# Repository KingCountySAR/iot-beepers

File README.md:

# SAR Beepers

A dedicated, loud pager for SAR callouts. It's a cheap ESP32 box on the member's home Wi-Fi with a buzzer alarm, status and alert LEDs, a button and an arm/quiet switch. The central server forwards pages to it, tracks who received and acknowledged them, monitors device health, and pushes firmware updates.

```
 callout source ──POST /api/ingest/page──┐
 web UI "Send page" ─────────────────────┤
                                         ▼
                ┌───────────────────────────────────────┐
                │ server (Node, Hono)                   │
                │  • REST API + React web UI            │      wss://host/mqtt
                │  • embedded MQTT broker (aedes) ──────┼──────────────────────► pagers
                │  • Postgres (Drizzle)                 │◄── status/ack/events ──
                │  • firmware store + OTA rollout       │
                └───────────────────────────────────────┘
```

| Dir | What |
|---|---|
| `server/` | Hono API, embedded MQTT broker, Drizzle/Postgres. Tests in `server/test` |
| `web/` | Vite + React admin and member UI |
| `firmware/` | ESP-IDF app ([firmware/README.md](firmware/README.md)) |
| `deploy/` | Its app on the KCSARA VM (the [vm](../vm) repo) |
| `hardware/` | Carrier board for the XIAO ESP32C3 ([rev1](hardware/rev1/README.md)) |
| `docs/` | [protocol](docs/protocol.md), [hardware behaviour](docs/hardware.md), [metrics](docs/metrics.md) |

## How a member sets up a pager
1. Plug it in. The green LED is mostly on: it's in setup mode.
2. On a phone, join the `SAR-Pager-xxxx` Wi-Fi. The setup page opens; if it doesn't, browse to `http://192.168.4.1`.
3. Choose the home Wi-Fi, enter its password, and confirm the server URL. The pager joins the network, registers with the server, and shows a **pairing code** and link.
4. Rejoin home Wi-Fi, open the link, sign in, and pick which channels the pager should alarm for.
5. The green LED settles to a short blip every 5 s. Press the button: one chirp means all good.

Pairing happens on the server, never on the device. The pager only holds a random secret, so no member passwords live on it. Channel choices are made from any browser, and a replacement pager is just a re-pair.

## Design notes
- **Embedded broker.** For 20–100 devices, an in-process MQTT broker means one container and no broker credentials to keep in sync. Device auth checks the DB directly. Each device can only use its own `dev/<id>/…` topics.
- **MQTT over WebSocket on 443.** One port and one TLS certificate (the VM's Caddy and Let's Encrypt), and it gets through hotel/guest networks.
- **Delivery tracking.** Every page has per-device *sent / received / acknowledged* timestamps. Devices that were offline get unexpired pages replayed when they reconnect. Pages older than 10 min arrive silently (LED only), so nobody gets a 3 am alarm for yesterday's mission.
- **Silent failure is the enemy.** The dashboard lists paired pagers that are offline, and the pager itself chirps if it can't reach the server for 30 min.
- **OTA with rollback.** Uploaded images are validated (project name and version are read from the image). You can pin one device to a version to canary it, then make it the default. A bad image rolls itself back.
- **Postgres in production, PGlite in dev/tests.** With no `DATABASE_URL`, the server runs Postgres-in-WASM in-process, so there's nothing to install locally. It runs the same SQL and migrations.

## Development
Requires Node 22+.

```sh
npm install
cp server/.env.example server/.env.local   # then put your email in SITE_ADMINS
npm run dev                          # UI :4100 (Vite, proxies /api and /mqtt to the server on :4102), metrics :4101
npm test                             # server integration tests (PGlite)
TEST_DATABASE_URL=postgres://postgres:pw@localhost:5432/postgres npm test   # same, against real Postgres
```

Open http://localhost:4100 and sign in with your `SITE_ADMINS` email. In dev, `DEV_LOGIN=true` lets you type an email instead of going through Google (treated as managed by its address's domain, which must be one of `ALLOWED_DOMAINS`). Create a channel, then pair a device.

The UI is on :4100 and metrics on :4101 in production too. Dev ports and URLs come from `server/dev.env`; `server/.env` overrides them, and `server/.env.local` (gitignored, for your own settings) overrides both.

**Without hardware**, simulate a device with the helpers in `server/test/harness.ts`. They do the same register → MQTT → hello flow as the firmware.

**Schema changes:** edit `server/src/db/schema.ts`. Until the first release we don't keep migrations: delete `server/drizzle/`, run `npm run db:generate -w server` to regenerate `0000_init`, and update existing databases by hand (or delete `server/data/` in dev). Migrations run on startup.

**Pages by email:** mail to `<channel slug>@beepers.kingcountysar.org` pages that channel, through the KCSARA VM's
mail service (the vm repo's [mail/README.md](../vm/mail/README.md)), which checks SPF and DKIM and POSTs it to
`/api/ingest/email` with `INGEST_TOKEN`. The subject is the page's title and the text its body, without a signature
after "-- ". An unknown channel bounces. To set it up: a route in the VM's `config/mail.env`, with `INGEST_TOKEN` and
who may send, and an MX record for `beepers.kingcountysar.org` pointing at the mail host:

```
ROUTE_BEEPERS=beepers.kingcountysar.org http://beepers:4100/api/ingest/email
ROUTE_BEEPERS_TOKEN=<INGEST_TOKEN>
ROUTE_BEEPERS_SENDERS=<who may page: addresses, or @domain>
```

Send a page from another system:

```sh
curl -X POST https://host/api/ingest/page \
  -H "Authorization: Bearer $INGEST_TOKEN" -H "Content-Type: application/json" \
  -d '{"channel":"callout","title":"Callout","body":"Lost hiker near Mt Si trailhead."}'
```

## Deploy
It runs on the KCSARA VM as the app `beepers`, at https://beepers.kingcountysar.org, deployed by the [vm](../vm) repo
(see "Apps" in its README). The VM's Caddy gives it its certificate and proxies the site, `/mqtt` included, and it uses
the VM's shared Postgres, cedar and Hydra over the `kcsara` network. `deploy/compose.yaml` runs the build on
`node:22-alpine`: `npm run build` makes one bundle, `server/dist/beepers.mjs`, which `deploy/app.json` sends with the
migrations (`server/drizzle`) and the web UI (`web/dist`). Firmware images are in the database.

The first time, from the vm repo:

1. `node deploy.mjs database beepers`: its database and user, in `apps/beepers/config/database.env` on the VM.
2. A Hydra client for cedar: `node hydra.mjs create oauth2-client --name beepers --grant-type client_credentials --scope members.read --format json`.
3. On the VM, `apps/beepers/config/app.env` from [deploy/app.env.example](deploy/app.env.example): `PUBLIC_URL`, the
   admins and domains, the Google client (below), the Hydra client, and `INGEST_TOKEN`.
4. DNS for `beepers.kingcountysar.org` pointed at the VM (or a test name in `HOSTS=`, in `apps/beepers/config/compose.env`,
   with `PUBLIC_URL` to match).

Then, and for each deploy: `npm run build` here, and `node deploy.mjs app ../beepers` from the vm repo.
`node deploy.mjs logs beepers` shows its log. Pagers reconnect by themselves after a deploy.

The VM's Prometheus collects its metrics (the `kcsara.metrics` label; see [docs/metrics.md](docs/metrics.md)), and its
health checks ask for `/healthz`.

**Running the build in Docker** on a dev machine, as on the VM: with `docker compose up` running in ../vm, make its
database once (`docker compose exec postgres createdb -U postgres beepers` there), then `npm run build` and
`npm run docker -- up -d` here (`npm run docker -- down` stops it). It's on http://localhost:4100, with the settings from
`server/dev.env`, `.env` and `.env.local`, then `server/.env.docker.local` for what differs in Docker. See
[deploy/compose.local.yaml](deploy/compose.local.yaml).

**Sign-in** is Google only, with Google's sign-in button (no redirects), as in rad-portal: anyone whose account is managed by one of the Workspace domains in `ALLOWED_DOMAINS` can sign in, and admins are the emails in `SITE_ADMINS` (changes take effect on restart). **Which channels** a member can join comes from their groups in the member database, mapped to channels on the **Access** page, plus any direct grants an admin adds there. A daily sync drops subscriptions people no longer qualify for. See [docs/members.md](docs/members.md). To create the OAuth client:
1. In [Google Cloud Console](https://console.cloud.google.com/), pick or create a project. Under **Google Auth Platform → Branding**, set the app name and support email.
2. Under **Audience**, choose **External** (members use their own Google accounts) and **publish** the app. It only asks for name and email, so Google doesn't need to review it. Left in testing mode, only listed test users can sign in.
3. Under **Clients**, create a **Web application** client with the **Authorized JavaScript origins** `https://beepers.kingcountysar.org` (`PUBLIC_URL`) and, for dev, `http://localhost:4100`. It needs no redirect URIs. Put its client ID in `GOOGLE_CLIENT_ID`; there's no secret to keep.

Google only allows plain-HTTP origins on localhost, so in dev sign in at http://localhost:4100, not `http://10.1.1.142:4100`.

**Firmware:** run `firmware/build.sh <board>` and upload the `dist/` image on the **Firmware** page. Members can then flash new pagers from the **Flash** page in Chrome or Edge, and updates roll out over Wi-Fi per board. See [firmware/README.md](firmware/README.md).

## Not done yet
- **Ingest from SMS.** The plumbing is `POST /api/ingest/page`: a Twilio number could call it.
- **Notify members when their pager goes offline**, by email/SMS. The dashboard already lists offline paired pagers.
- Rate limiting on `/api/device/register`.
- Signed firmware images (see docs/hardware.md).
- A custom PCB: see docs/hardware.md for the daughter-board sketch and the alarm drive options.

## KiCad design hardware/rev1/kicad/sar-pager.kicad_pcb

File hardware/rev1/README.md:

# Rev 1 carrier board: schematic and BOM (for review)

A small 2-layer board (52 × 32 mm) that carries a **Seeed XIAO ESP32C3** and adds the alarm, two LEDs, a button and the arm/quiet switch. JLCPCB assembles all the surface-mount parts. You hand-solder the XIAO (14 joints), the buzzer (2), the 10 mm LED (2) and the slide switch (5).

Status: **draft board** in [`kicad/`](kicad/): placed, autorouted and DRC-clean, but not yet checked against real parts. See [Board draft](#board-draft) and [Before ordering](#before-ordering).

## Power
Power comes from USB-C on the XIAO, from a phone charger. The board takes `5V` (VBUS) and `3V3` from the XIAO's pins and needs no regulator of its own. The XIAO's battery pads are left unused for now.

## Schematic

```
                         XIAO ESP32C3 (U1)
                     ┌────────────────────────┐
                     │ D0  GPIO2   (strap) nc │
       ALARM_GATE ◄──┤ D1  GPIO3              │
       BUTTON     ───┤ D2  GPIO4              │
       SWITCH     ───┤ D3  GPIO5              │
                     │ D4  GPIO6  SDA      nc │  ← kept free for a future I²C screen
                     │ D5  GPIO7  SCL      nc │
       LED_GREEN  ◄──┤ D6  GPIO21             │
                     │ D7  GPIO20          nc │
                     │ D8  GPIO8   (strap) nc │
                     │ D9  GPIO9   (strap) nc │  ← on-board BOOT button, also works as the button
       LED_RED    ◄──┤ D10 GPIO10             │
             +5V  ◄──┤ 5V                     │
                     │ 3V3                 nc │
             GND  ───┤ GND                    │
                     └────────────────────────┘

Alarm (low-side switch). A MOSFET rather than driving from the GPIO: the transducer
wants ~5 Vp-p and up to ~100 mA, more than a pin should supply.

     +5V ──┬──────────── R1 ──────┬────────┐
           │         10 Ω 1206    │        │
          C1 10µF                BZ1+      D1 1N4148W
           │                      │ BZ1    │ (cathode to BZ1+)
          GND                    BZ1-      │
                                  ├────────┘
                                  │ D
       ALARM_GATE ── R2 ──┬──── G Q1 AO3400A
                    100 Ω │       │ S
                         R3 100k  │
                          │       │
                         GND     GND

     R3 holds the gate low while the ESP32 is in reset or booting, so the alarm
     can't sound during power-up or a firmware update.
     R1 sets the volume. Tune it on the chosen part; use 0 Ω for 5 V-rated parts.

LEDs (driven straight from the GPIO pins)

     LED_GREEN ── R4 100 Ω ──►|── GND     LED2 green 0805, status (~5 mA)
     LED_RED   ── R5 100 Ω ──►|── GND     LED1 red 10 mm diffused, alert (~13 mA)

Inputs (internal pull-ups enabled in firmware)

     BUTTON ── SW1 ── GND                 tactile; the 3D-printed case has the large cap
     SWITCH ── SW2 common
               SW2 pos A ── GND           = quiet
               SW2 pos B ── nc            = armed (pulled up)
```

### Alarm part (BZ1)
The board draft uses a **standard 12 mm passive magnetic buzzer**: the common 12 × 9.5 mm (or 12 × 8.5 mm) through-hole part with 7.6 mm pin spacing, rated 5 V, with a coil of about 16 Ω and resonance around 2.3–2.7 kHz. The long lead (or the `+` mark) goes to the square pad. Run the firmware with `Alarm drive → Square wave`, and set `CONFIG_NOTIFIER_ALARM_FREQ_HZ` to the part's resonant frequency; generic ones vary, so sweep it by ear on the sample.

R1 sets the volume. Start with 10 Ω and measure the current: these coils are rated around 30–40 mA, so lower R1 (down to 0 Ω) for a louder alarm or raise it to soften it.

The same circuit also takes the other candidates that fit the footprint, with only R1 and the firmware mode changing:

| Candidate | R1 | Firmware `Alarm drive` |
|---|---|---|
| Generic 12 mm passive magnetic, 5 V, 16 Ω (draft default) | 10 Ω (tune) | Square wave at its resonance |
| PUI **AT-1224-TWT-5V-2-R**, magnetic, 2.4 kHz, 5 V | 0 Ω | Square wave, 2400 Hz |
| 12 mm 5 V active buzzer, e.g. PUI **AI-1223-TWT-5V-R** or Cylewet CYT1036 | 0 Ω | On/off; D1 not needed but harmless |

The SMD Huaneng **MLT-8530** (LCSC C94599) would let JLCPCB place the buzzer too, but it needs a different footprint.

## BOM
"Basic" means a JLCPCB basic part (no per-order feeder fee). Where the listing didn't say, the status is marked unconfirmed; JLCPCB's BOM upload will show it.

| Ref | Qty | Part | Package | LCSC / source | JLCPCB | Notes |
|---|---|---|---|---|---|---|
| U1 | 1 | Seeed XIAO ESP32C3 | Module, castellated | Amazon (you have them) | Hand-solder | Footprint has castellated pads **and** 2.54 mm holes, so pin headers also fit |
| Q1 | 1 | AO3400A N-MOSFET, 30 V 5.7 A, Vgs(th) 1.45 V | SOT-23 | C20917 | Basic | Fully on at 3.3 V gate drive |
| D1 | 1 | 1N4148W | SOD-123 | C81598 | Unconfirmed (common basic part) | Flyback for the coil |
| BZ1 | 1 | 12 mm passive magnetic buzzer, 5 V, ~16 Ω (see above) | THT, 7.6 mm pitch | Amazon/LCSC | Hand-solder | 2 joints |
| R1 | 1 | 10 Ω 1%, 250 mW | 1206 | C17903 | Unconfirmed | Volume; 0 Ω for 5 V parts |
| R2 | 1 | 100 Ω 1% | 0603 | C22775 | Unconfirmed | Gate series resistor |
| R3 | 1 | 100 kΩ 1% | 0603 | C25803 | Unconfirmed | Gate pull-down |
| R4, R5 | 2 | 100 Ω 1% | 0603 | C22775 | Unconfirmed | LED current |
| C1 | 1 | 10 µF 25 V X5R | 0805 | C15850 | Unconfirmed | Local reservoir for alarm pulses |
| LED2 | 1 | Green LED, KT-0805G, 430 mcd @ 5 mA | 0805 | C2297 | Unconfirmed | Status; bright, so PWM dimming may be worth adding |
| LED1 | 1 | Red LED, 10 mm, diffused, wide angle (~300 mcd, 50–60°) | Through-hole, 2.54 mm | Digi-Key/Amazon | Hand-solder | Stands up through the lid, visible across a room |
| SW1 | 1 | Tactile switch, TS-1187A-B-A-B, 5.1×5.1 mm | SMD | C318884 | Basic | The case's printed button presses it |
| SW2 | 1 | Slide switch SPDT, right angle, C&K OS102011MA1QN1 | THT | C226259 (LCSC; Digi-Key backordered) | Hand-solder | 5 joints. Its 2 × 4 mm lever sticks out through the case wall |
| H1–H2 | 2 | M2.5 mounting holes | | | | For 3D-printed case standoffs |

Most of the assembled parts' basic/extended status is unconfirmed; JLCPCB's BOM upload shows any extended-part fees.

## Board draft

The KiCad 10 project is in [`kicad/`](kicad/): open `sar-pager.kicad_pro`. More renders are in [`kicad/renders/`](kicad/renders/). The 3D view has no models for the XIAO or SW1, so they show as bare pads.

**Layout (52 × 32 mm, 2 layers, 1.6 mm):**
- **XIAO (U1):** on the left, with its USB-C end flush with the board edge so the cable comes in through the case wall. No vias under it, because its underside has exposed battery and test pads.
- **Top edge:** the buzzer (BZ1) and the 10 mm red LED (LED1), the two things that need lid openings.
- **Alarm driver:** Q1, D1, R1 (volume), R2, R3 and C1 sit together between the buzzer and the XIAO.
- **Right:** the button (SW1), with the green LED (LED2) next to it.
- **Bottom edge, under the XIAO:** the arm/quiet slide switch (SW2), with its body flush with the board edge. Its 2 mm wide lever sticks out 4 mm past the board, about 1.5 mm past a 2 mm case wall, so it can be flipped with a fingertip. The wall slot needs about 4.5 × 2.5 mm for the lever and its 2 mm of travel.
- **Mounting:** three M2.5 holes (H1–H3) for case standoffs.
- **Ground:** filled on both layers. 5 V and the buzzer loop use 0.5 mm tracks, signals 0.25 mm. The rules suit JLCPCB's standard process (0.2 mm clearance, 0.3/0.6 mm vias).

**Antenna:** the XIAO ESP32C3 uses the **external FPC antenna** on its u.FL connector. The case needs a spot to stick it to an inside wall, away from the buzzer's magnet and coil.

**Case:** LED1 is mounted tall (leads left long, or on a printed spacer) so it sits flush with or proud of the lid. LED2 shows through a short piece of 1/16" clear acrylic rod glued into the lid. The 3D-printed lid needs holes for LED1, LED2, the button cap over SW1 and the sound port over BZ1, plus wall cut-outs for USB-C and SW2's lever. The case is in [`case/`](case/README.md).

### How it was made, and how to change it
`generate.py` places the parts and assigns the nets, Freerouting routes the board, and `finish.py` adds the ground fill. `./build.sh` runs all of that, then DRC, renders and fab files. It needs KiCad 10 and Docker.

That route is only for the first draft. **Now that the board exists, edit `sar-pager.kicad_pcb` in KiCad**, then run `./build.sh fab` to re-check it and re-export. A full `./build.sh` would regenerate the board and overwrite any hand edits. There's no schematic yet: the nets come from the table in `generate.py`, which follows the schematic above.

**Outputs of `./build.sh fab`** (in `kicad/fab/`, not committed):
- `sar-pager-gerbers.zip`: Gerbers and drill files for JLCPCB
- `bom-jlcpcb.csv` and `cpl-jlcpcb.csv`: the assembly BOM (LCSC part numbers) and placement file. The hand-soldered parts are left out.
- `drc.rpt`: the DRC report

## Before ordering
This is a draft. Check these before sending it to a fab:
- [ ] **XIAO footprint.** It's drawn from Seeed's published dimensions: 21 × 17.8 mm, pin rows 15.24 mm apart, pins centred along the length. Compare it with Seeed's official KiCad footprint, or print the board 1:1 and lay a XIAO on it.
- [ ] **Buzzer.** Check the sample's pin spacing (7.6 mm) and polarity, and its height (9.5 mm) against the case.
- [ ] **Slide switch.** Confirm which lever position connects pin 2 to pin 1 (GND = quiet), and label the case to match. Check that the lever sticks out far enough once the case is printed; thinning the wall around the slot gains about 1 mm.
- [ ] **JLCPCB rotations.** Check the parts in JLCPCB's placement preview after uploading the CPL file. SOT-23 and polarized parts (D1, LED2, Q1) sometimes need a rotation correction.
- [ ] **LED2 brightness.** 430 mcd at about 5 mA may be glaring at night. Raise R4 if so.
- [ ] **A schematic.** For anything beyond this draft, capture the schematic in KiCad so ERC and "Update PCB from schematic" work.

## Firmware
The defaults in `firmware/main/Kconfig.projbuild` match this pin map: alarm GPIO3, button GPIO4 plus BOOT (GPIO9), switch GPIO5, green LED GPIO21, red LED GPIO10. The default is square-wave drive at 2700 Hz. Logs go over the XIAO's USB-C (USB-Serial-JTAG), which leaves GPIO20/21 free.

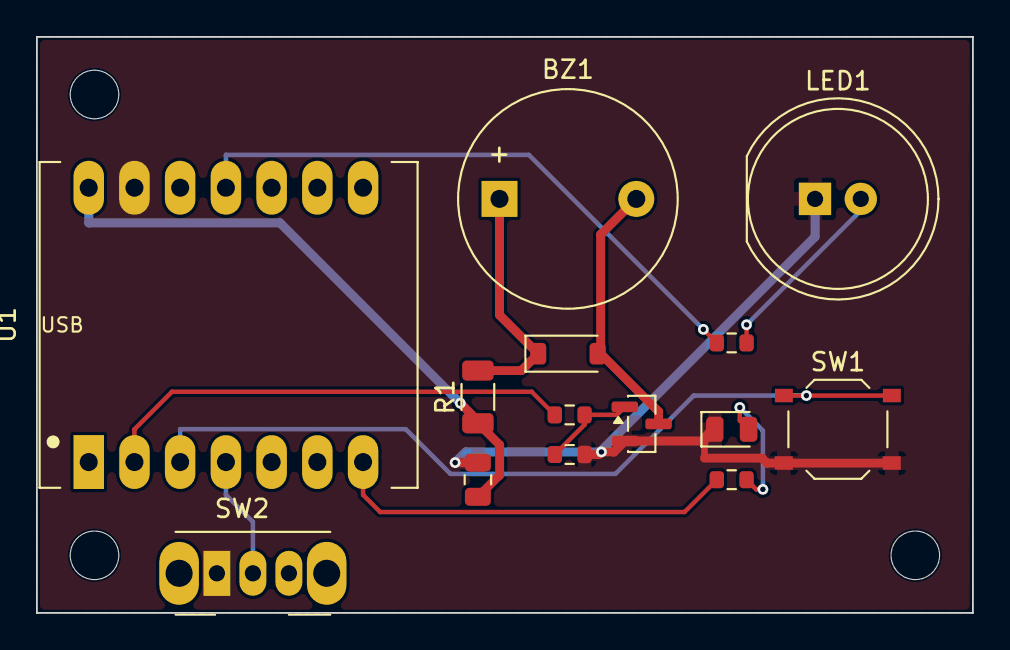
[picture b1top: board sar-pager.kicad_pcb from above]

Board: 2 copper layers, 52.0 x 32.0 mm, 17 parts (0 on the bottom side), 12 nets.

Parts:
BZ1: 12mm passive 5V; Buzzer_12x9.5RM7.6
C1: 10uF; C_0805_2012Metric
D1: 1N4148W; D_SOD-123
H1, H2, H3: M2.5; MountingHole_2.7mm_M2.5
LED1: Red 10mm diffused; LED_D10.0mm
LED2: Green; LED_0805_2012Metric
Q1: AO3400A; SOT-23
R1: 10R; R_1206_3216Metric
R2, R4, R5: 100R; R_0603_1608Metric
R3: 100k; R_0603_1608Metric
SW1: TS-1187A-B-A-B; SW_Push_1P1T_XKB_TS-1187A
SW2: OS102011MA1QN1; SW_Slide_SPDT_Angled_CK_OS102011MA1Q
U1: XIAO_ESP32C3; Seeed_XIAO_ESP32C3

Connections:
+5V: C1.1, R1.1, U1.14
ALARM: R2.1, U1.2
BUTTON: SW1.1, U1.3
BZ_N: BZ1.2, D1.2, Q1.3
BZ_P: BZ1.1, D1.1, R1.2
GATE: Q1.1, R2.2, R3.1
GND: C1.2, LED1.1, LED2.1, Q1.2, R3.2, SW1.2, SW2.1, U1.13
LED_G: R4.1, U1.7
LED_G_A: LED2.2, R4.2
LED_R: R5.1, U1.11
LED_R_A: LED1.2, R5.2
SWITCH: SW2.2, U1.4
